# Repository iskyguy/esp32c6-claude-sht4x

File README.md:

# ESP32-C6 + SHT41 battery sensor node

A small battery-powered temperature/humidity node built around the bare
ESP32-C6 chip, meant to run ESPHome over Wi-Fi now and Zigbee (802.15.4) later.

**Status: schematic and PCB layout, revision B** (revision A plus the changes
from a design review, listed under "Revision B changes"). Nothing has been
built or tested. The layout passes KiCad's design rules check but was routed
by script and needs a human review before ordering (see below).

| File | What it is |
|---|---|
| `hardware/esp32c6-sht4x.kicad_pro` | KiCad 10 project (open this) |
| `hardware/esp32c6-sht4x.kicad_sch` | Schematic, saved by KiCad 10.0.8 |
| `hardware/esp32c6-sht4x.kicad_pcb` | PCB layout, 4 layers, 50 x 26 mm |
| `hardware/lib/esp32c6-sht4x.kicad_sym` | Project symbol for the ESP32-C6FH8 |
| `docs/schematic.pdf` | Printable schematic |
| `docs/bom.csv` | Bill of materials exported from the schematic |
| `docs/erc.rpt` | KiCad electrical rules check report (0 violations) |
| `docs/drc.rpt` | KiCad design rules check report for the PCB (0 violations, 0 unconnected, schematic parity clean) |
| `docs/pcb-*.png` | Renders of the board and its outer copper layers |
| `tools/` | The Python scripts that generated the schematic and the layout (reference only, paths are specific to the machine they ran on) |

## What is on the board

| Block | Part | Notes |
|---|---|---|
| MCU | ESP32-C6FH8 (QFN32) | Bare chip, 8 MB in-package flash, Wi-Fi 6 + BLE + 802.15.4. 40 MHz crystal. The 4 MB ESP32-C6FH4 is a drop-in alternative. |
| Antenna | Johanson 2450AT18A100E chip antenna | One 2.4 GHz antenna serves Wi-Fi and Zigbee/Thread. Two pi networks on the 50 ohm feed: C16-L2-C17 at the chip pin (chip matching and harmonic filter, fitted) and C23-L3-C24 at the antenna (antenna tuning, 0R and not-fitted until tuned). |
| USB | USB-C 16-pin receptacle | 5.1 k on CC1/CC2, D+/D- to the chip's native USB Serial/JTAG (GPIO13/GPIO12) for flashing and logs, USBLC6-2 ESD protection. |
| Charger | TI BQ24074 | 1-cell Li-ion/LiPo charger with power path: the board runs from USB while the battery charges, and from the battery otherwise. |
| Regulator | XC6220B331MR | 3.3 V, 700 mA, about 8 uA quiescent current. |
| Sensor | Sensirion SHT41-AD1B | I2C address 0x44. |
| I2C ports | 2 x JST-SH 4-pin (Qwiic / STEMMA QT) | Pin 1 GND, 2 3V3, 3 SDA, 4 SCL. |
| OLED | 1x4 2.54 mm socket | GND, VCC, SCL, SDA: the order used by common 0.91"/0.96" SSD1306 modules. |
| Battery | JST-PH 2-pin, side entry | Pin 1 BAT+, pin 2 GND. |
| Controls | RESET and BOOT buttons, status LED, charge LED | |

### Switched peripheral rail

The SHT41, both Qwiic ports, the OLED header and the I2C pull-ups sit on
`VPERIPH`, which is 3V3 behind a P-channel MOSFET (Q1). The firmware turns it
on by driving GPIO3 low. It is off at power-up and during deep sleep, so
add-on boards with power LEDs do not drain the battery while the node sleeps.
Bridging solder jumper JP1 makes the rail permanently on.

## GPIO map

| GPIO | Function |
|---|---|
| 2 | Battery voltage, VBAT / 2 (ADC1_CH2) |
| 3 | `PERIPH_EN_N`, low = peripheral rail on |
| 8 | Strapping pin, 10 k pull-up |
| 9 | BOOT button (low at reset = download mode) |
| 12 / 13 | USB D- / D+ |
| 14 | Status LED, active high |
| 16 / 17 | UART0 TX / RX on test pads TP1 / TP2 |
| 20 | `CHG_N`, low while charging |
| 21 | `PGOOD_N`, low while USB power is present |
| 22 / 23 | I2C SDA / SCL |
| 0, 1, 4-7, 15, 18, 19 | Unused |

## Charger settings

- Charge current is set by R4: I = 890 / R4. 3.6 k gives about 250 mA, which is
  safe for cells of 250 mAh and up. Use 1.8 k for about 500 mA with larger cells.
- EN2 low and EN1 high select the 500 mA USB input limit. R3 (ILIM) is only
  used if that mode is changed.
- TS has a fixed 10 k resistor because a 2-pin battery has no thermistor.
- TMR and ITERM are left open for the default safety timers and 10 %
  termination current.

## PCB layout

- 50 x 26 mm, 4 layers, 1.6 mm. Layer 2 is a solid ground plane, layer 3 is a
  3V3 plane, and both outer layers carry signals with ground pours.
- All parts are on the top side. 0.15 mm tracks and clearances, 0.5/0.3 mm
  vias, which fits standard 4-layer services.
- The SHT41 sits alone on a peninsula in the top-left corner, cut off by a
  1 mm slot on two sides. There is no copper pour on any layer there, and the
  only copper crossing the 4.5 mm bridge is four 0.15 mm traces.
- The chip antenna is in the top-right corner with all four copper layers
  cleared around it (5.2 x 7.75 mm). The ground edge now sits right below the
  antenna feed pad, so the 0.35 mm feed runs over the layer-2 ground plane for
  all but its last 0.35 mm. Nothing is routed on the bottom layer under the
  RF chain.
- Both crystal traces are on the top layer only, with solid ground on layers
  2 and 4 underneath and no signals or vias under the crystal.
- USB D+/D- run as one 0.2 mm / 0.16 mm gap pair on the bottom layer from the
  connector, past the ESD part, to series footprints at the chip.
- USB-C is on the right edge, the battery connector on the bottom edge, one
  Qwiic port on the top edge and one on the bottom edge, and the OLED socket
  along the top edge.
- The charger and regulator, the warm parts, are about 30 mm from the sensor.

### Review this before ordering

The layout was placed by hand and routed by a script, then checked with
KiCad's DRC. DRC only proves the copper is connected and spaced correctly.
A person should still look at:

- **Stackup.** No fab stackup is chosen yet. The 0.35 mm RF feed and the
  0.2/0.16 mm USB pair assume roughly 0.2 mm of prepreg between the outer and
  inner layers (for example JLCPCB's JLC04161H-7628). Recalculate both for
  the real stackup.
- **Antenna geometry.** The antenna position and clearance were not checked
  against Johanson's mounting drawing for the 2450AT18A100E (the datasheet
  could not be opened while designing). Compare before ordering.
- **RF values.** C16/L2/C17 (1.5 pF / 2.0 nH / 1.5 pF) are placeholders so
  the board is not built with an open filter. They and C23/L3/C24 must be
  set with a network analyser on the built board.
- **USB pair.** The two lines separate for about 2 mm at the chip-side vias
  and widen to 0.6 mm pitch for 3 mm beside the ESD part. The pair references
  the 3V3 plane on the bottom layer.
- **EN.** The pull-up and capacitor are now 2.5 mm from the pin, but the
  branch to the reset button is still about 35 mm long because the button is
  on the other side of the board.
- **Trace aesthetics and return paths.** The autorouted traces are valid but
  not tidy, and some signals cross the board on the bottom layer.
- **Decoupling.** Several ESP32-C6 supply pins reach their capacitors through
  the 3V3 plane rather than by a direct trace.
- **No mounting holes** and no fiducials yet.
- Footprints are the stock KiCad ones and have not been checked against the
  exact parts in the BOM.

### Revision B changes

Made in response to a review of revision A:

1. RF: chip-side pi network is now fitted, and a separate antenna tuning pi
   (C23, L3, C24) was added next to the antenna.
2. Antenna feed: ground boundary moved up to the feed pad, so the feed is over
   ground almost to the antenna. The antenna clearance itself is kept.
3. Regulator: 10 uF input (C4) and 10 uF output (C5) capacitors sit directly
   at the VIN, VOUT and GND pins with 0.4 mm traces.
4. RF supply: pins 2/3 leave on a 0.3 mm trace, C13 (100 nF) and C14 (now
   10 uF) are after L1, and the 1 uF (C15) is before it. The ESP32-C6 exposed
   pad has 9 ground vias, the charger pad has 4.
5. Crystal: both legs on the top layer with no vias, R11 stays as the series
   tuning position, nothing routed underneath.
6. USB: routed as a pair, 2 vias per line instead of 5 and 2, about 34 mm
   per line, ground vias at the layer changes, and 0R series (R20, R21) plus
   not-fitted shunt capacitor (C25, C26) footprints at the chip.
7. EN: R14 and C21 moved next to the pin, with the reset button as a branch.
8. The BOM has a Spec column with dielectric, voltage and tolerance.
9. The status LED and its resistor moved next to the test points.

## SHT41 layout rules

These follow Sensirion's SHT4x design-in guidance and are what keeps the
reading at ambient rather than at board temperature.

1. Put the SHT41 in a corner or on a tab at the board edge, as far as possible
   from the ESP32-C6, the BQ24074, the regulator and the charge LED. Put the
   heat sources at the opposite end.
2. Mill a slot (about 1 mm wide) around the sensor so it sits on a small
   peninsula connected by a narrow bridge.
3. No copper pour on any layer under or around the sensor inside the slot. Cut
   the ground plane out there.
4. Route VDD, GND, SDA and SCL over the bridge as thin traces (0.15 mm or less).
   No vias under the part.
5. Keep C22 (100 nF) next to the sensor's VDD pin, on the peninsula.
6. If the board is mounted vertically, the sensor goes at the bottom so warm
   air from the other parts rises away from it.
7. The enclosure needs an opening right at the sensor, with the sensor's air
   volume sealed from the warm interior where possible.
8. Use no-clean solder paste and do not wash, coat or pot the sensor. Keep the
   opening on top of the package free of flux and dust.
9. In firmware, keep the node asleep between readings and measure soon after
   wake-up, before the radio has warmed the board.

Other layout notes: keep the antenna at a board edge with the keep-out from the
Johanson datasheet and no copper under it, keep the antenna and the sensor at
opposite ends, route the RF trace as 50 ohm, keep the crystal close to the chip,
and place all connectors (USB-C, battery, Qwiic) on board edges.

## ESPHome starting point

Untested until hardware exists.

```yaml
esp32:
  board: esp32-c6-devkitc-1
  variant: esp32c6
  flash_size: 8MB
  framework:
    type: esp-idf

switch:
  - platform: gpio            # peripheral rail (SHT41, Qwiic, OLED)
    id: periph_power
    pin:
      number: GPIO3
      inverted: true
    restore_mode: ALWAYS_ON

i2c:
  sda: GPIO22
  scl: GPIO23
  scan: false

sensor:
  - platform: sht4x
    temperature:
      name: Temperature
    humidity:
      name: Humidity
  - platform: adc
    pin: GPIO2
    attenuation: 12db
    name: Battery voltage
    filters:
      - multiply: 2.0

binary_sensor:
  - platform: gpio
    name: Charging
    pin: {number: GPIO20, inverted: true}
  - platform: gpio
    name: USB power
    pin: {number: GPIO21, inverted: true}

status_led:
  pin: GPIO14
```

## Check before ordering

These could not be confirmed against datasheets while drawing the schematic
and should be checked by a person:

- **Battery polarity.** J2 pin 1 is BAT+. JST-PH batteries are not
  standardised, so compare the footprint against the actual battery before
  plugging one in. There is no reverse-polarity protection.
- **BQ24074 details** (charge-current constant, open TMR/ITERM behaviour, 10 k
  on TS) were taken from memory of the TI datasheet.
- **ESP32-C6FH8 pinout** comes from Espressif's own KiCad symbol for the
  pin-compatible ESP32-C6FH4.
- **Crystal.** No exact part is chosen. The design assumes a 40 MHz,
  2.0 x 1.6 mm, 10 pF load, 10 ppm crystal with pads 1 and 3 as the crystal.
  The 12 pF load capacitors must be recalculated for the chosen part.
- **Battery.** No cell is specified. Check that it accepts about 250 mA of
  charge current and has its own protection circuit. The board has no cell
  protection, no reverse-polarity protection and no battery thermistor.
- **Capacitors.** The BOM gives dielectric and voltage, not manufacturer part
  numbers.
- **Antenna matching** values must be tuned on the real PCB.

## Credits

The ESP32-C6 symbol is derived from
[espressif/kicad-libraries](https://github.com/espressif/kicad-libraries)
(CC-BY-SA 4.0). All other symbols are from the standard KiCad 10 libraries.

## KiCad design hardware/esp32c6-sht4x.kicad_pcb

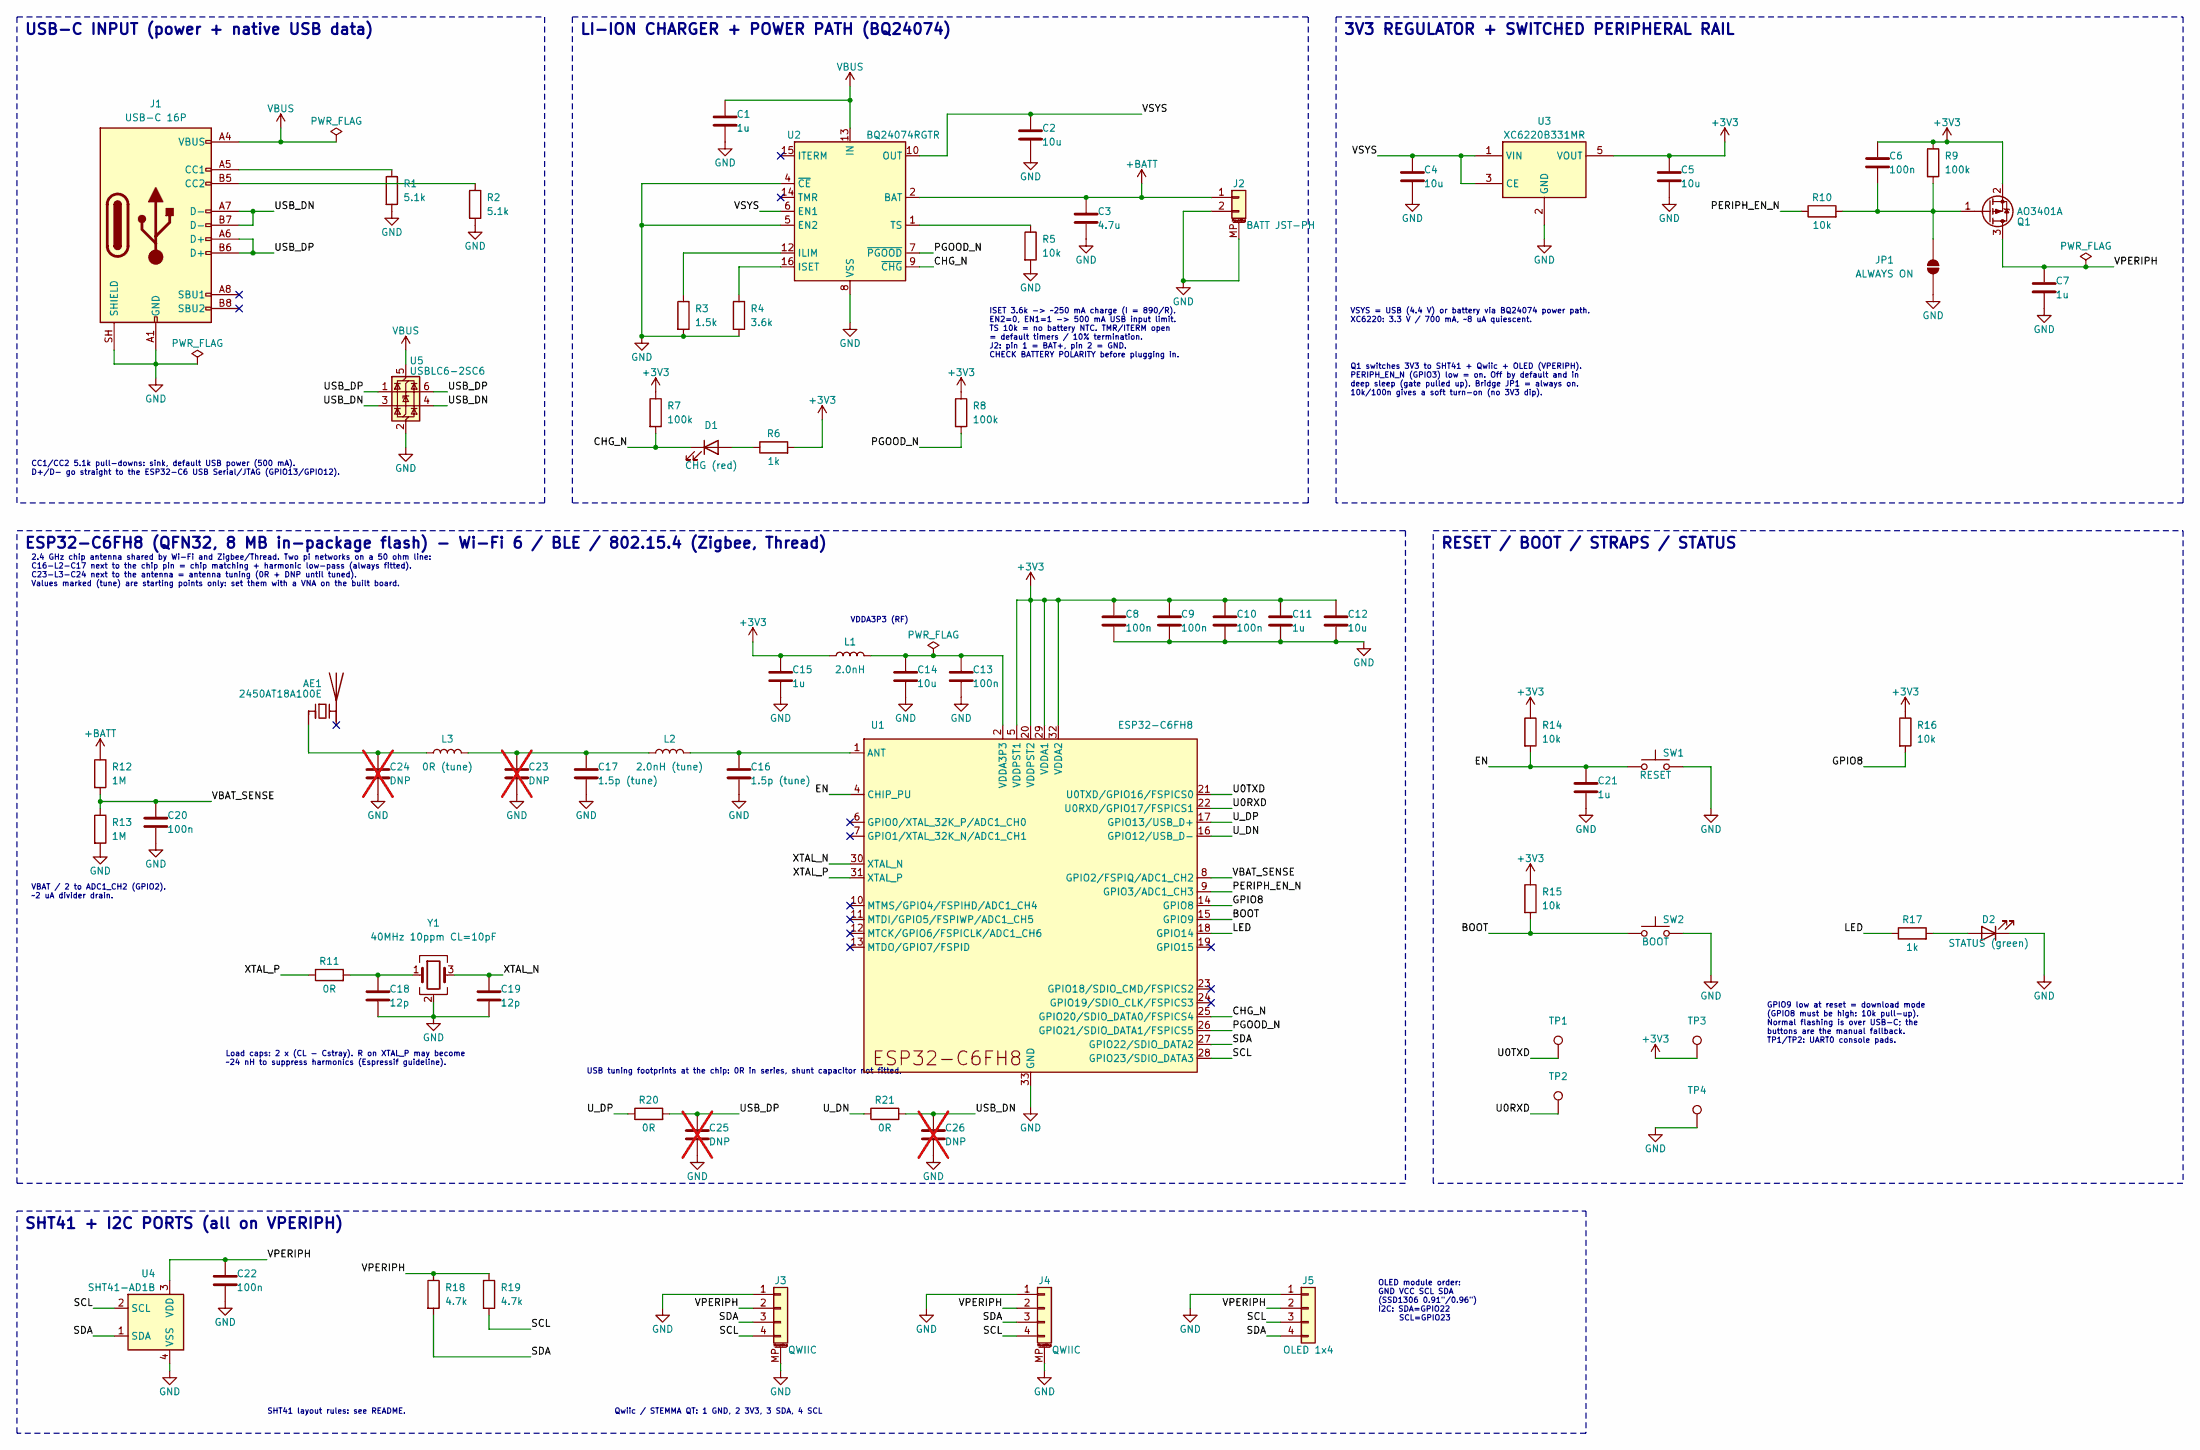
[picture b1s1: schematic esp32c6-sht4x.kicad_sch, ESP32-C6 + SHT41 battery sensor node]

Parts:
AE1: 2450AT18A100E; Johanson_2450AT18x100; MPN Johanson 2450AT18A100E
C1, C7, C11, C15, C21: 1u; C_0402_1005Metric
C2, C4, C5, C12, C14: 10u; C_0603_1608Metric
C3: 4.7u; C_0402_1005Metric
C6, C8, C9, C10, C13, C20, C22: 100n; C_0402_1005Metric
C16, C17: 1.5p (tune); C_0402_1005Metric
C18, C19: 12p; C_0402_1005Metric
C23, C24, C25, C26: DNP; C_0402_1005Metric; not fitted
D1: CHG (red); LED_0603_1608Metric
D2: STATUS (green); LED_0603_1608Metric
J1: USB-C 16P; USB_C_Receptacle_GCT_USB4105-xx-A_16P_TopMnt_Horizontal; MPN GCT USB4105-GF-A
J2: BATT JST-PH; JST_PH_S2B-PH-SM4-TB_1x02-1MP_P2.00mm_Horizontal; MPN JST S2B-PH-SM4-TB
J3, J4: QWIIC; JST_SH_SM04B-SRSS-TB_1x04-1MP_P1.00mm_Horizontal; MPN JST SM04B-SRSS-TB
J5: OLED 1x4; PinSocket_1x04_P2.54mm_Vertical
JP1: ALWAYS ON; SolderJumper-2_P1.3mm_Open_RoundedPad1.0x1.5mm
L1: 2.0nH; L_0402_1005Metric
L2: 2.0nH (tune); L_0402_1005Metric
L3: 0R (tune); L_0402_1005Metric
Q1: AO3401A; SOT-23
R1, R2: 5.1k; R_0402_1005Metric
R3: 1.5k; R_0402_1005Metric
R4: 3.6k; R_0402_1005Metric
R5, R10, R14, R15, R16: 10k; R_0402_1005Metric
R6, R17: 1k; R_0402_1005Metric
R7, R8, R9: 100k; R_0402_1005Metric
R11, R20, R21: 0R; R_0402_1005Metric
R12, R13: 1M; R_0402_1005Metric
R18, R19: 4.7k; R_0402_1005Metric
SW1: RESET; SW_SPST_B3U-1000P
SW2: BOOT; SW_SPST_B3U-1000P
TP1: U0TXD; TestPoint_Pad_D1.0mm
TP2: U0RXD; TestPoint_Pad_D1.0mm
TP3: 3V3; TestPoint_Pad_D1.0mm
TP4: GND; TestPoint_Pad_D1.0mm
U1: ESP32-C6FH8; QFN-32-1EP_5x5mm_P0.5mm_EP3.6x3.6mm; MPN ESP32-C6FH8
U2: BQ24074RGTR; VQFN-16-1EP_3x3mm_P0.5mm_EP1.6x1.6mm
U3: XC6220B331MR; SOT-23-5
U4: SHT41-AD1B; Sensirion_DFN-4_1.5x1.5mm_P0.8mm_SHT4x_NoCentralPad
U5: USBLC6-2SC6; SOT-23-6
Y1: 40MHz 10ppm CL=10pF; Crystal_SMD_2016-4Pin_2.0x1.6mm

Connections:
+3V3: C5.1, C6.1, C8.1, C9.1, C10.1, C11.1, C12.1, C15.1, L1.1, Q1.2 (S), R6.2, R7.1, R8.1, R9.1, R14.1, R15.1, R16.1, TP3.1, U1.5 (VDDPST1), U1.20 (VDDPST2), U1.29 (VDDA1), U1.32 (VDDA2), U3.5 (VOUT)
+BATT: C3.1, J2.1, R12.1, U2.2 (BAT), U2.3 (BAT)
/BOOT: R15.2, SW2.1, U1.15 (GPIO9)
/CHG_N: D1.1 (K), R7.2, U1.25 (GPIO20/SDIO_DATA0/FSPICS4), U2.9 (~CHG)
/EN: C21.1, R14.2, SW1.1, U1.4 (CHIP_PU)
/GPIO8: R16.2, U1.14 (GPIO8)
/LED: R17.1, U1.18 (GPIO14)
/PERIPH_EN_N: R10.1, U1.9 (GPIO3/ADC1_CH3)
/PGOOD_N: R8.2, U1.26 (GPIO21/SDIO_DATA1/FSPICS5), U2.7 (~PGOOD)
/SCL: J3.4, J4.4, J5.3, R19.2, U1.28 (GPIO23/SDIO_DATA3), U4.2 (SCL)
/SDA: J3.3, J4.3, J5.4, R18.2, U1.27 (GPIO22/SDIO_DATA2), U4.1 (SDA)
/U0RXD: TP2.1, U1.22 (U0RXD/GPIO17/FSPICS1)
/U0TXD: TP1.1, U1.21 (U0TXD/GPIO16/FSPICS0)
/USB_DN: C26.1, J1.A7 (D-), J1.B7 (D-), R21.2, U5.3 (I/O2), U5.4 (I/O2)
/USB_DP: C25.1, J1.A6 (D+), J1.B6 (D+), R20.2, U5.1 (I/O1), U5.6 (I/O1)
/U_DN: R21.1, U1.16 (GPIO12/USB_D-)
/U_DP: R20.1, U1.17 (GPIO13/USB_D+)
/VBAT_SENSE: C20.1, R12.2, R13.1, U1.8 (GPIO2/FSPIQ/ADC1_CH2)
/VPERIPH: C7.1, C22.1, J3.2, J4.2, J5.2, Q1.3 (D), R18.1, R19.1, U4.3 (VDD)
/VSYS: C2.1, C4.1, U2.6 (EN1), U2.10 (OUT), U2.11 (OUT), U3.1 (VIN), U3.3 (CE)
/XTAL_N: C19.1, U1.30 (XTAL_N), Y1.3
/XTAL_P: R11.1, U1.31 (XTAL_P)
GND: C1.2, C2.2, C3.2, C4.2, C5.2, C7.2, C8.2, C9.2, C10.2, C11.2, C12.2, C13.2, C14.2, C15.2, C16.2, C17.2, C18.2, C19.2, C20.2, C21.2, C22.2, C23.2, C24.2, C25.2, C26.2, D2.1 (K), J1.A1 (GND), J1.A12 (GND), J1.B1 (GND), J1.B12 (GND), J1.SH (SHIELD), J2.2, J2.MP (MountPin), J3.1, J3.MP (MountPin), J4.1, J4.MP (MountPin), J5.1, JP1.1 (A), R1.2, R2.2, R3.2, R4.2, R5.2, R13.2, SW1.2, SW2.2, TP4.1, U1.33 (GND), U2.4 (~CE), U2.5 (EN2), U2.8 (VSS), U2.17 (VSS), U3.2 (GND), U4.4 (VSS), U5.2 (GND), Y1.2 (G), Y1.4 (G)
unnamed: AE1.1 (FEED), C24.1, L3.1
unnamed: C13.1, C14.1, L1.2, U1.2 (VDDA3P3), U1.3 (VDDA3P3)
unnamed: C17.1, C23.1, L2.1, L3.2
unnamed: C18.1, R11.2, Y1.1
unnamed: D1.2 (A), R6.1
unnamed: D2.2 (A), R17.2
unnamed: J1.A5 (CC1), R1.1
unnamed: J1.B5 (CC2), R2.1
unnamed: C6.2, JP1.2 (B), Q1.1 (G), R9.2, R10.2
unnamed: C16.1, L2.2, U1.1 (ANT)
unnamed: R3.1, U2.12 (ILIM)
unnamed: R4.1, U2.16 (ISET)
unnamed: R5.1, U2.1 (TS)
VBUS: C1.1, J1.A4 (VBUS), J1.A9 (VBUS), J1.B4 (VBUS), J1.B9 (VBUS), U2.13 (IN), U5.5 (VBUS)

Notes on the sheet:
Qwiic / STEMMA QT: 1 GND, 2 3V3, 3 SDA, 4 SCL
Q1 switches 3V3 to SHT41 + Qwiic + OLED (VPERIPH). PERIPH_EN_N (GPIO3) low = on. Off by default and in deep sleep (gate pulled up). Bridge JP1 = always on. 10k/100n gives a soft turn-on (no 3V3 dip).
VDDA3P3 (RF)
OLED module order: GND VCC SCL SDA (SSD1306 0.91"/0.96") I2C: SDA=GPIO22 SCL=GPIO23
SHT41 + I2C PORTS (all on VPERIPH)
ESP32-C6FH8 (QFN32, 8 MB in-package flash) - Wi-Fi 6 / BLE / 802.15.4 (Zigbee, Thread)
VSYS = USB (4.4 V) or battery via BQ24074 power path. XC6220: 3.3 V / 700 mA, ~8 uA quiescent.
2.4 GHz chip antenna shared by Wi-Fi and Zigbee/Thread. Two pi networks on a 50 ohm line: C16-L2-C17 next to the chip pin = chip matching + harmonic low-pass (always fitted). C23-L3-C24 next to the antenna = antenna tuning (0R + DNP until tuned). Values marked (tune) are starting points only: set t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
USB-C INPUT (power + native USB data)
ISET 3.6k -> ~250 mA charge (I = 890/R). EN2=0, EN1=1 -> 500 mA USB input limit. TS 10k = no battery NTC. TMR/ITERM open = default timers / 10% termination. J2: pin 1 = BAT+, pin 2 = GND. CHECK BATTERY POLARITY before plugging in.
CC1/CC2 5.1k pull-downs: sink, default USB power (500 mA). D+/D- go straight to the ESP32-C6 USB Serial/JTAG (GPIO13/GPIO12).
LI-ION CHARGER + POWER PATH (BQ24074)
Load caps: 2 x (CL - Cstray). R on XTAL_P may become ~24 nH to suppress harmonics (Espressif guideline).
GPIO9 low at reset = download mode (GPIO8 must be high: 10k pull-up). Normal flashing is over USB-C; the buttons are the manual fallback. TP1/TP2: UART0 console pads.
3V3 REGULATOR + SWITCHED PERIPHERAL RAIL
RESET / BOOT / STRAPS / STATUS
SHT41 layout rules: see README.
USB tuning footprints at the chip: 0R in series, shunt capacitor not fitted.
VBAT / 2 to ADC1_CH2 (GPIO2). ~2 uA divider drain.

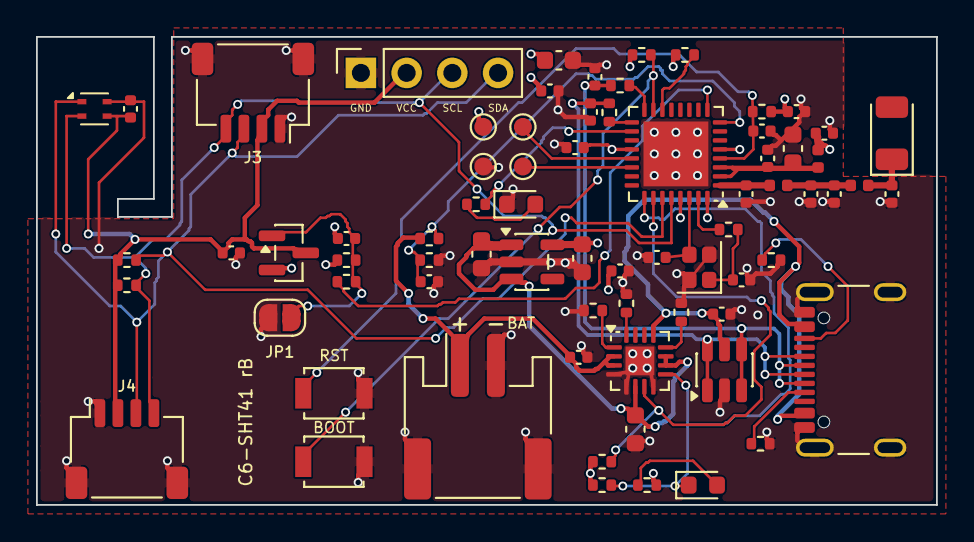
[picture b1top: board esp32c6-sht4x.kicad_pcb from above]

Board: 4 copper layers, 50.0 x 26.0 mm, 72 parts (0 on the bottom side), 37 nets.

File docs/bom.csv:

"Reference","Value","Footprint","MPN","Spec","QUANTITY","DNP"
"AE1","2450AT18A100E","RF_Antenna:Johanson_2450AT18x100","Johanson 2450AT18A100E","","1",""
"C1","1u","Capacitor_SMD:C_0402_1005Metric","","25V X5R 10%","1",""
"C2,C4,C5,C12,C14","10u","Capacitor_SMD:C_0603_1608Metric","","10V X5R 20%, >=4.7u effective at 4.4V bias","5",""
"C3","4.7u","Capacitor_SMD:C_0402_1005Metric","","10V X5R 10%","1",""
"C6,C8-C10,C13,C20,C22","100n","Capacitor_SMD:C_0402_1005Metric","","16V X7R 10%","7",""
"C7,C11,C15,C21","1u","Capacitor_SMD:C_0402_1005Metric","","10V X5R 10%","4",""
"C16,C17","1.5p (tune)","Capacitor_SMD:C_0402_1005Metric","","50V C0G +/-0.1pF","2",""
"C18,C19","12p","Capacitor_SMD:C_0402_1005Metric","","50V C0G 5%","2",""
"C23-C26","DNP","Capacitor_SMD:C_0402_1005Metric","","50V C0G","4","DNP"
"D1","CHG (red)","LED_SMD:LED_0603_1608Metric","","","1",""
"D2","STATUS (green)","LED_SMD:LED_0603_1608Metric","","","1",""
"J1","USB-C 16P","Connector_USB:USB_C_Receptacle_GCT_USB4105-xx-A_16P_TopMnt_Horizontal","GCT USB4105-GF-A","","1",""
"J2","BATT JST-PH","Connector_JST:JST_PH_S2B-PH-SM4-TB_1x02-1MP_P2.00mm_Horizontal","JST S2B-PH-SM4-TB","","1",""
"J3,J4","QWIIC","Connector_JST:JST_SH_SM04B-SRSS-TB_1x04-1MP_P1.00mm_Horizontal","JST SM04B-SRSS-TB","","2",""
"J5","OLED 1x4","Connector_PinSocket_2.54mm:PinSocket_1x04_P2.54mm_Vertical","","","1",""
"JP1","ALWAYS ON","Jumper:SolderJumper-2_P1.3mm_Open_RoundedPad1.0x1.5mm","","","1",""
"L1","2.0nH","Inductor_SMD:L_0402_1005Metric","","RF multilayer, high Q","1",""
"L2","2.0nH (tune)","Inductor_SMD:L_0402_1005Metric","","RF multilayer, high Q","1",""
"L3","0R (tune)","Inductor_SMD:L_0402_1005Metric","","0R jumper or RF inductor after tuning","1",""
"Q1","AO3401A","Package_TO_SOT_SMD:SOT-23","","","1",""
"R1,R2","5.1k","Resistor_SMD:R_0402_1005Metric","","1% 1/16W","2",""
"R3","1.5k","Resistor_SMD:R_0402_1005Metric","","1% 1/16W","1",""
"R4","3.6k","Resistor_SMD:R_0402_1005Metric","","1% 1/16W","1",""
"R5,R10,R14-R16","10k","Resistor_SMD:R_0402_1005Metric","","1% 1/16W","5",""
"R6,R17","1k","Resistor_SMD:R_0402_1005Metric","","1% 1/16W","2",""
"R7-R9","100k","Resistor_SMD:R_0402_1005Metric","","1% 1/16W","3",""
"R11","0R","Resistor_SMD:R_0402_1005Metric","","1% 1/16W","1",""
"R12,R13","1M","Resistor_SMD:R_0402_1005Metric","","1% 1/16W","2",""
"R18,R19","4.7k","Resistor_SMD:R_0402_1005Metric","","1% 1/16W","2",""
"R20,R21","0R","Resistor_SMD:R_0402_1005Metric","","0R jumper (USB series tuning)","2",""
"SW1","RESET","Button_Switch_SMD:SW_SPST_B3U-1000P","","","1",""
"SW2","BOOT","Button_Switch_SMD:SW_SPST_B3U-1000P","","","1",""
"TP1","U0TXD","TestPoint:TestPoint_Pad_D1.0mm","","","1",""
"TP2","U0RXD","TestPoint:TestPoint_Pad_D1.0mm","","","1",""
"TP3","3V3","TestPoint:TestPoint_Pad_D1.0mm","","","1",""
"TP4","GND","TestPoint:TestPoint_Pad_D1.0mm","","","1",""
"U1","ESP32-C6FH8","Package_DFN_QFN:QFN-32-1EP_5x5mm_P0.5mm_EP3.6x3.6mm","ESP32-C6FH8","","1",""
"U2","BQ24074RGTR","Package_DFN_QFN:VQFN-16-1EP_3x3mm_P0.5mm_EP1.6x1.6mm","","","1",""
"U3","XC6220B331MR","Package_TO_SOT_SMD:SOT-23-5","","","1",""
"U4","SHT41-AD1B","Sensor_Humidity:Sensirion_DFN-4_1.5x1.5mm_P0.8mm_SHT4x_NoCentralPad","","","1",""
"U5","USBLC6-2SC6","Package_TO_SOT_SMD:SOT-23-6","","","1",""
"Y1","40MHz 10ppm CL=10pF","Crystal:Crystal_SMD_2016-4Pin_2.0x1.6mm","","","1",""

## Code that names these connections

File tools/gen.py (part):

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wire(cc1, (64, cc1[1])); down('R', '5.1k', (64, cc1[1]))
wire(cc2, (76, cc2[1])); down('R', '5.1k', (76, cc2[1]))
dn1, dn2, dp1, dp2 = J1.pin('A7'), J1.pin('B7'), J1.pin('A6'), J1.pin('B6')
wire(dn1, (dn1[0] + 2, dn1[1]), (dn2[0] + 2, dn2[1]), dn2); wire((dn1[0] + 2, dn1[1]), (dn1[0] + 5, dn1[1])); label((dn1[0] + 5, dn1[1]), 'USB_DN')
wire(dp1, (dp1[0] + 2, dp1[1]), (dp2[0] + 2, dp2[1]), dp2); wire((dp2[0] + 2, dp2[1]), (dp2[0] + 5, dp2[1])); label((dp2[0] + 5, dp2[1]), 'USB_DP')
nc(J1.pin('A8')); nc(J1.pin('B8'))
g = J1.pin('A1'); sh = J1.pin('SH')
wire(g, (g[0], g[1] + 4)); wire(sh, (sh[0], sh[1] + 2), (g[0], sh[1] + 2)); gnd((g[0], g[1] + 4)); wire((g[0], sh[1] + 2), (g[0] + 6, sh[1] + 2)); flag((g[0] + 6, sh[1] + 2))
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stub(U5, 1, 'USB_DP'); stub(U5, 3, 'USB_DN'); stub(U5, 6, 'USB_DP'); stub(U5, 4, 'USB_DN')
p = U5.pin(5); wire(p, (p[0], p[1] - 2)); pwr('VBUS', (p[0], p[1] - 2))
p = U5.pin(2); wire(p, (p[0], p[1] + 2)); gnd((p[0], p[1] + 2))
text(12, 86, 'CC1/CC2 5.1k pull-downs: sink, default USB power (500 mA).\nD+/D- go straight to the ESP32-C6 USB Serial/JTAG (GPIO13/GPIO12).', 1.0)

# ================================================================ B: charger
box(90, 22, 196, 92, 'LI-ION CHARGER + POWER PATH (BQ24074)')
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wire(ilim, (106, ilim[1]), (106, 62)); r = two('R', '1.5k', 106, 65);
wire(iset, (114, iset[1]), (114, 62)); r2 = two('R', '3.6k', 114, 65)
wire((100, 68), (114, 68)); gnd((100, 68))
wire(en1, (en1[0] - 3, en1[1])); label((en1[0] - 3, en1[1]), 'VSYS', 'l')
p = U2.pin(8); wire(p, (p[0], p[1] + 4)); gnd((p[0], p[1] + 4))
o = U2.pin(10)
wire(o, (o[0] + 4, o[1]), (o[0] + 4, 36), (172, 36)); label((172, 36), 'VSYS'); down('C', '10u', (156, 36), **C0603_10U)
b = U2.pin(2)
J2P = (182, b[1]); wire(b, J2P); down('C', '4.7u', (164, b[1])); wire((172, b[1]), (172, b[1] - 2)); pwr('+BATT', (172, b[1] - 2))
J2 = place('Connector_Generic_MountingPin', 'Conn_01x02_MountingPin', 'J2', 'BATT JST-PH', 186, b[1],
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ts = U2.pin(1); wire(ts, (156, ts[1])); down('R', '10k', (156, ts[1]))
stub(U2, 7, 'PGOOD_N'); stub(U2, 9, 'CHG_N')
# charge LED + status pull-ups
label((98, 84), 'CHG_N', 'l'); wire((98, 84), (107, 84))
D1 = place('Device', 'LED', 'D1', 'CHG (red)', 110, 84, fp='LED_SMD:LED_0603_1608Metric',
           refpos=(110, 81.4, 0, 'bottom'), valpos=(110, 86, 0, 'top'))
r = two('R', '1k', 119, 84, horiz=True); wire((113, 84), r.a); wire(r.b, (126, 84), (126, 80)); pwr('+3V3', (126, 80))
r = up('R', '100k', (102, 82)); wire((102, 82), (102, 84))
label((140, 84), 'PGOOD_N', 'l'); wire((140, 84), (146, 84), (146, 82)); up('R', '100k', (146, 82))
text(150, 64, 'ISET 3.6k -> ~250 mA charge (I = 890/R).\nEN2=0, EN1=1 -> 500 mA USB input limit.\nTS 10k = no battery NTC. TMR/ITERM open\n= default timers / 10% termination.\nJ2: pin 1 = BAT+, pin 2 = GND.\nCHECK BATTERY POLARITY before plugging in.', 1.0)

# ================================================================ C: LDO + peripheral switch
box(200, 22, 322, 92, '3V3 REGULATOR + SWITCHED PERIPHERAL RAIL')
U3 = place('Regulator_Linear', 'XC6220B331MR', 'U3', 'XC6220B331MR', 230, 44)
vi = U3.pin(1); cep = U3.pin(3)
wire(vi, (206, vi[1])); label((206, vi[1]), 'VSYS', 'l'); down('C', '10u', (211, vi[1]), **C0603_10U)
wire(cep, (cep[0] - 2, cep[1]), (cep[0] - 2, vi[1]))
p = U3.pin(2); wire(p, (p[0], p[1] + 2)); gnd((p[0], p[1] + 2))
vo = U3.pin(5); wire(vo, (256, vo[1]), (256, vo[1] - 2)); pwr('+3V3', (256, vo[1] - 2)); down('C', '10u', (248, vo[1]), **C0603_10U)
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c = two('C', '100n', 278, 43); wire(c.b, (278, g_[1]))
r = two('R', '100k', 286, 43); wire(r.b, (286, g_[1]))
rs = two('R', '10k', 270, g_[1], horiz=True); wire(rs.b, g_)
wire(rs.a, (264, g_[1])); label((264, g_[1]), 'PERIPH_EN_N', 'l')
JP1 = place('Jumper', 'SolderJumper_2_Open', 'JP1', 'ALWAYS ON', 286, 58, 90,
            fp='Jumper:SolderJumper-2_P1.3mm_Open_RoundedPad1.0x1.5mm',
            refpos=(279, 57, 90, None), valpos=(279, 59, 90, None))
wire((286, g_[1]), (286, 54)); gnd((286, 62))
wire(d_, (d_[0], 58), (312, 58)); label((312, 58), 'VPERIPH'); down('C', '1u', (302, 58)); flag((308, 58))
text(202, 64, 'VSYS = USB (4.4 V) or battery via BQ24074 power path.\nXC6220: 3.3 V / 700 mA, ~8 uA quiescent.', 1.0)
text(202, 72, 'Q1 switches 3V3 to SHT41 + Qwiic + OLED (VPERIPH).\nPERIPH_EN_N (GPIO3) low = on. Off by default and in\ndeep sleep (gate pulled up). Bridge JP1 = always on.\n10k/100n gives a soft turn-on (no 3V3 dip).', 1.0)

# ================================================================ D: ESP32-C6
box(10, 96, 210, 190, 'ESP32-C6FH8 (QFN32, 8 MB in-package flash) - Wi-Fi 6 / BLE / 802.15.4 (Zigbee, Thread)')
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for n in (10, 11, 12, 13): nc(U1.pin(n))
# right side
for n, name in ((21, 'U0TXD'), (22, 'U0RXD'), (17, 'U_DP'), (16, 'U_DN'), (8, 'VBAT_SENSE'), (9, 'PERIPH_EN_N'),
                (14, 'GPIO8'), (15, 'BOOT'), (18, 'LED'), (25, 'CHG_N'), (26, 'PGOOD_N'), (27, 'SDA'), (28, 'SCL')):
    stub(U1, n, name, 3)
for n in (19, 23, 24): nc(U1.pin(n))
# RF chain
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           refpos=(70, 152.5, 0, None), valpos=(70, 154.5, 0, None))
a, bb, gg = Y1.pin(1), Y1.pin(3), Y1.pin(2)
rx = two('R', '0R', 55, 160, horiz=True)
wire(rx.b, a); wire(rx.a, (48, 160)); label((48, 160), 'XTAL_P', 'l')
wire(bb, (80, 160)); label((80, 160), 'XTAL_N')
c1 = two('C', '12p', 62, 163); c2 = two('C', '12p', 78, 163)
wire((62, 166), (78, 166)); wire(gg, (70, 166)); gnd((70, 166))
text(40, 171, 'Load caps: 2 x (CL - Cstray). R on XTAL_P may become\n~24 nH to suppress harmonics (Espressif guideline).', 1.0)
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# vbat sense
pwr('+BATT', (22, 128)); ra = two('R', '1M', 22, 131); rb = two('R', '1M', 22, 139)
wire(ra.b, rb.a); gnd(rb.b)
wire((22, 135), (38, 135)); label((38, 135), 'VBAT_SENSE'); down('C', '100n', (30, 135))
text(12, 147, 'VBAT / 2 to ADC1_CH2 (GPIO2).\n~2 uA divider drain.', 1.0)

# ================================================================ E: buttons, straps, LED, test points
box(214, 96, 322, 190, 'RESET / BOOT / STRAPS / STATUS')
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up('R', '10k', (228, 152)); wire((228, 152), (228, 154))
SW2 = place('Switch', 'SW_Push', 'SW2', 'BOOT', 246, 154, fp='Button_Switch_SMD:SW_SPST_B3U-1000P')
wire((250, 154), (254, 154), (254, 160)); gnd((254, 160))
label((276, 130), 'GPIO8', 'l'); wire((276, 130), (282, 130), (282, 128)); up('R', '10k', (282, 128))
label((276, 154), 'LED', 'l'); r = two('R', '1k', 283, 154, horiz=True); wire((276, 154), r.a)
D2 = place('Device', 'LED', 'D2', 'STATUS (green)', 294, 154, 180, fp='LED_SMD:LED_0603_1608Metric',
           refpos=(294, 151.4, 0, 'bottom'), valpos=(294, 156, 0, 'top'))
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wire((252, 172), (246, 172)); pwr('+3V3', (246, 172))
tp = place('Connector', 'TestPoint', nref('TP'), 'GND', 252, 182, fp='TestPoint:TestPoint_Pad_D1.0mm', hide_value=True)
wire((252, 182), (246, 182)); gnd((246, 182))
text(262, 164, 'GPIO9 low at reset = download mode\n(GPIO8 must be high: 10k pull-up).\nNormal flashing is over USB-C; the\nbuttons are the manual fallback.\nTP1/TP2: UART0 console pads.', 1.0)

# ================================================================ F: sensor + I2C
box(10, 194, 236, 226, 'SHT41 + I2C PORTS (all on VPERIPH)')
U4 = place('Sensor_Humidity', 'SHT4x', 'U4', 'SHT41-AD1B', 30, 210)
stub(U4, 1, 'SDA', 3); stub(U4, 2, 'SCL', 3)
p = U4.pin(3); wire(p, (p[0], 201), (46, 201)); label((46, 201), 'VPERIPH'); down('C', '100n', (40, 201))
p = U4.pin(4); wire(p, (p[0], p[1] + 1)); gnd((p[0], p[1] + 1))
r1 = two('R', '4.7k', 70, 206); r2 = two('R', '4.7k', 78, 206)
wire((66, 203), (78, 203)); label((66, 203), 'VPERIPH', 'l')
wire(r1.b, (70, 215), (84, 215)); label((84, 215), 'SDA')
wire(r2.b, (78, 211), (84, 211)); label((84, 211), 'SCL')
def conn4(ref, val, x, names, fp, mp=True, mpn=None):
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        m = c.pin('MP'); wire(m, (m[0], m[1] + 1)); gnd((m[0], m[1] + 1))
conn4('J3', 'QWIIC', 120, ('VPERIPH', 'SDA', 'SCL'), 'Connector_JST:JST_SH_SM04B-SRSS-TB_1x04-1MP_P1.00mm_Horizontal', mpn='JST SM04B-SRSS-TB')
conn4('J4', 'QWIIC', 158, ('VPERIPH', 'SDA', 'SCL'), 'Connector_JST:JST_SH_SM04B-SRSS-TB_1x04-1MP_P1.00mm_Horizontal', mpn='JST SM04B-SRSS-TB')
conn4('J5', 'OLED 1x4', 196, ('VPERIPH', 'SCL', 'SDA'), 'Connector_PinSocket_2.54mm:PinSocket_1x04_P2.54mm_Vertical', mp=False)
text(206, 204, 'OLED module order:\nGND VCC SCL SDA\n(SSD1306 0.91"/0.96")\nI2C: SDA=GPIO22\n     SCL=GPIO23', 1.0)
text(96, 222.5, 'Qwiic / STEMMA QT: 1 GND, 2 3V3, 3 SDA, 4 SCL', 1.0)
text(46, 222.5, 'SHT41 layout rules: see README.', 1.0)

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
